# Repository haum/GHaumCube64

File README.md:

# GHaumCube64

Le GHaumCube64 est un jeu lumineux tridimentionnel sous forme de cube suspendu dans les airs.

État du projet : En cours

## Description générale

À l'heure actuelle, le projet est définit comme étant un cube de 64 (4×4×4) tåls (nom inventé pour désigner les éléments lumineux, munis chacun de trois leds multicolores adressables), orienté sur sa pointe et suspendu ; il y a aussi une manette de jeu à lui adjoindre. L'objectif est d'y programmer des jeux tels que morpion/snake/tron en 3D.

## Organisation des fichiers

```
<repo>
├── code
│   ├── cube <= Code du cube
│   └── remote <= Code de la télécommande/manette de jeu
│   └── Tal_test <= Code de test des LEDs
└── structure
    ├── placement
    │   ├── cube.blend <= disposition des tåls dans l'espace
    │   └── placement.scad <= disposition des tåls dans l'espace, d'un point de vue fabrication
    └── tal
        ├── tal.blend <= Modèle d'un tål complet
        ├── tal_bottom.stl.xz <= Export STL (compressé) de la partie basse
        ├── tal_top.stl.xz <= Export STL (compressé) de la partie haute
        └── Ball
            ├── support_led_Tal.FCStd <= Support LEDs FreeCAD file
            └── support_led_Tal.stl <= Export STL du support de LEDs
```

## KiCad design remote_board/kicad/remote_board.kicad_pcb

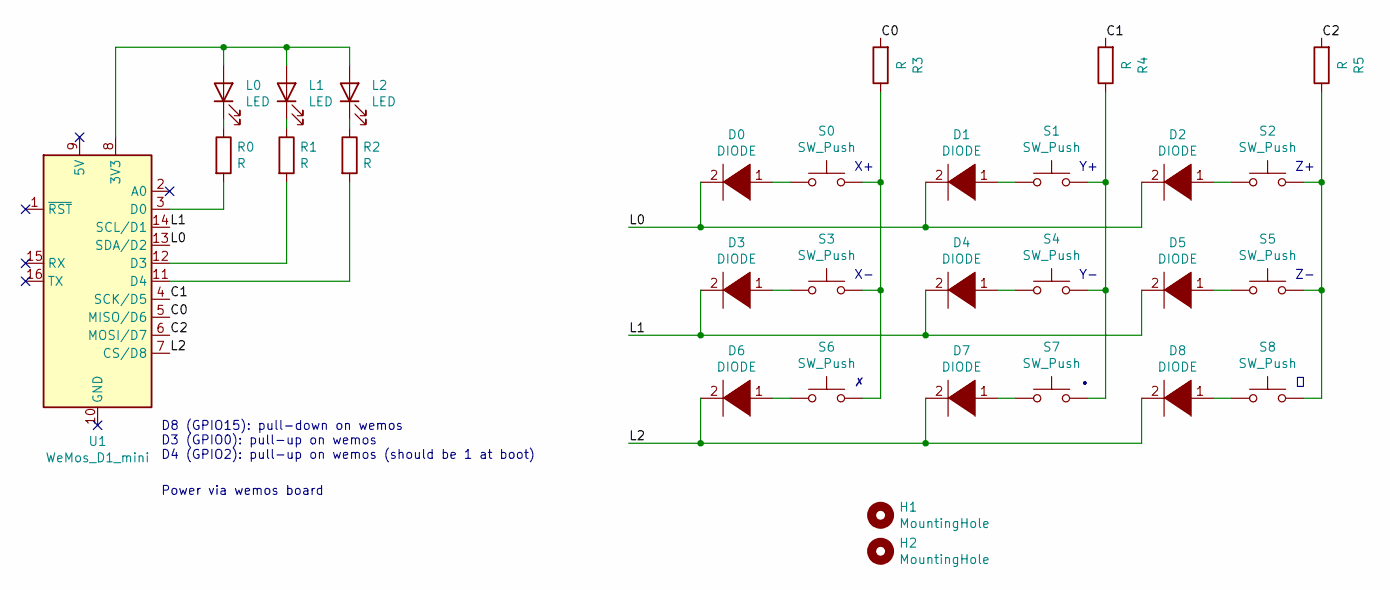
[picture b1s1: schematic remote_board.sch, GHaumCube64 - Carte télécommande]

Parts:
D0, D1, D2, D3, D4, D5, D6, D7, D8: DIODE; D_DO-35_SOD27_P10.16mm_Horizontal
H1, H2: MountingHole; MountingHole_5.3mm_M5
L0, L1, L2: LED; LED_D3.0mm
R0, R1, R2, R3, R4, R5: R; R_Axial_DIN0207_L6.3mm_D2.5mm_P15.24mm_Horizontal
S0, S1, S2, S3, S4, S5, S6, S7, S8: SW_Push; SW_PUSH_5mm_2pins
U1: WeMos_D1_mini; WEMOS_D1_mini_light

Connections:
/C0: R3.2, U1.5 (MISO/D6)
/C1: R4.2, U1.4 (SCK/D5)
/C2: R5.2, U1.6 (MOSI/D7)
/L0: D0.2 (A), D1.2 (A), D2.2 (A), U1.13 (SDA/D2)
/L1: D3.2 (A), D4.2 (A), D5.2 (A), U1.14 (SCL/D1)
/L2: D6.2 (A), D7.2 (A), D8.2 (A), U1.7 (CS/D8)
unnamed: D0.1 (K), S0.1
unnamed: D1.1 (K), S1.1
unnamed: D2.1 (K), S2.1
unnamed: D3.1 (K), S3.1
unnamed: D4.1 (K), S4.1
unnamed: D5.1 (K), S5.1
unnamed: D6.1 (K), S6.1
unnamed: D7.1 (K), S7.1
unnamed: D8.1 (K), S8.1
unnamed: L0.1 (K), R0.1
unnamed: L0.2 (A), L1.2 (A), L2.2 (A), U1.8 (3V3)
unnamed: L1.1 (K), R1.1
unnamed: L2.1 (K), R2.1
unnamed: R0.2, U1.3 (D0)
unnamed: R1.2, U1.12 (D3)
unnamed: R2.2, U1.11 (D4)
unnamed: R3.1, S0.2, S3.2, S6.2
unnamed: R4.1, S1.2, S4.2, S7.2
unnamed: R5.1, S2.2, S5.2, S8.2

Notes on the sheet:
D8 (GPIO15): pull-down on wemos D3 (GPIO0): pull-up on wemos D4 (GPIO2): pull-up on wemos (should be 1 at boot)
Power via wemos board

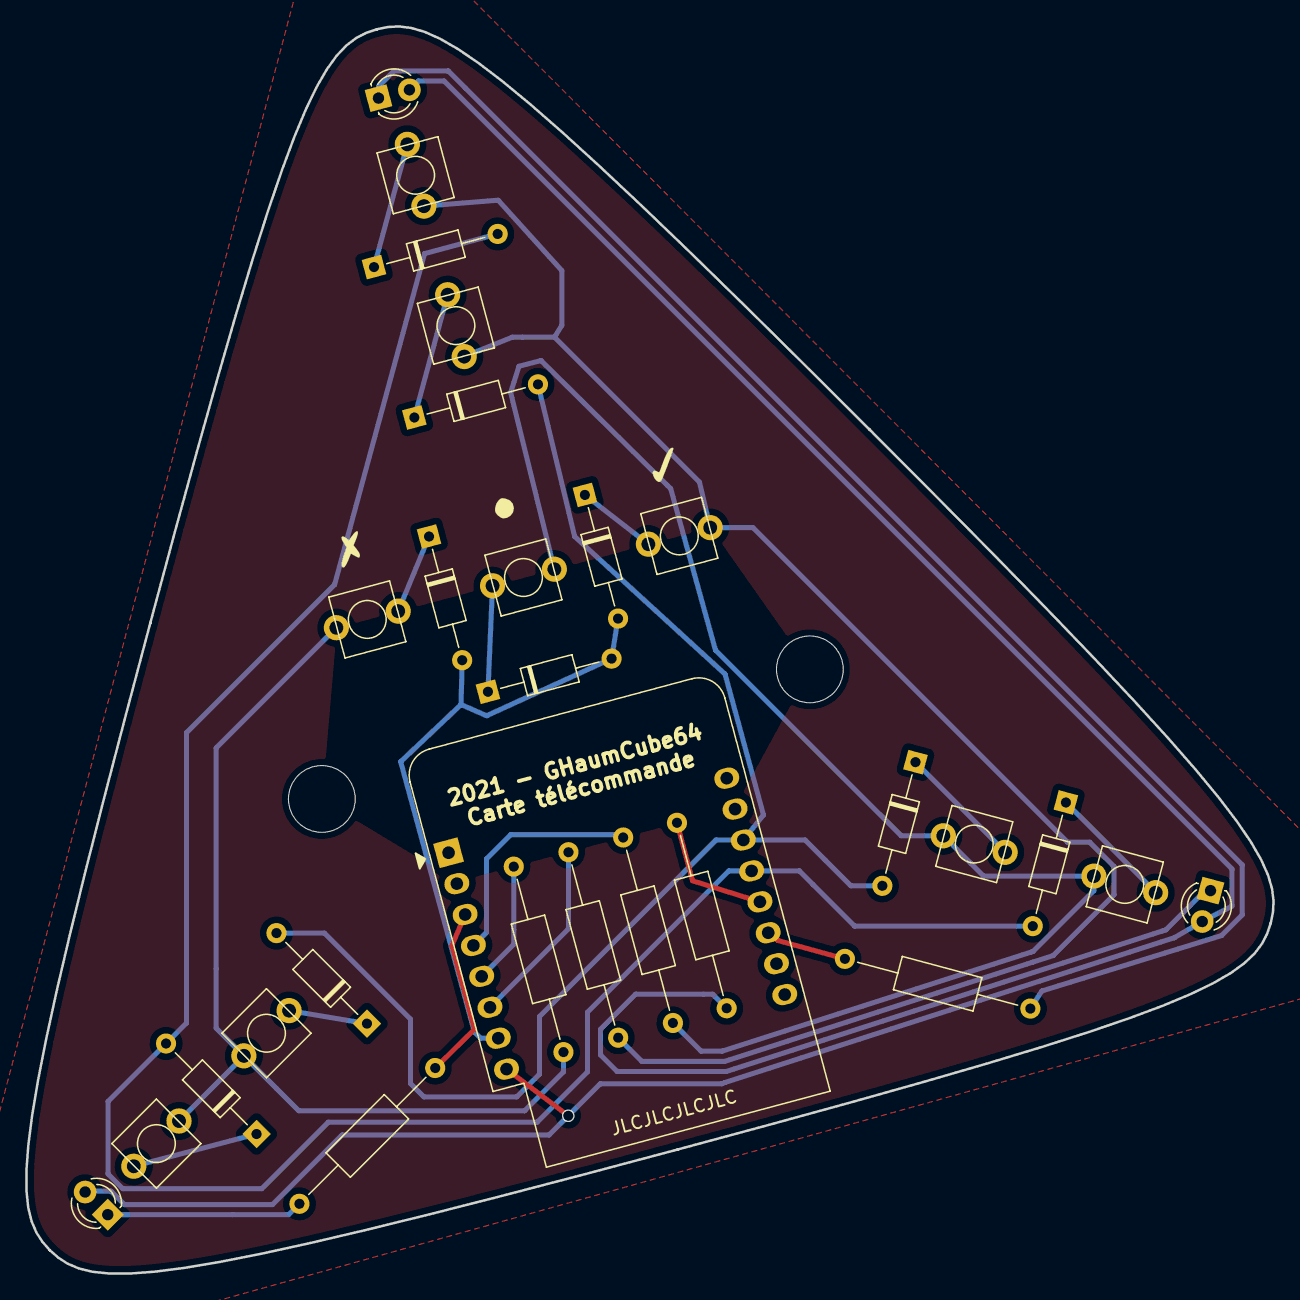
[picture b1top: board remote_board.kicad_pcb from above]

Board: 2 copper layers, 99.0 x 99.0 mm, 30 parts (0 on the bottom side), 25 nets.

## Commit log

2020-06-11 Add blender model of tål
2020-06-11 Add STL exports of tål
2020-06-11 Add visual expected 3D placement of the tåls in blender format
2020-06-11 Add structure placeholders for the code
2020-06-11 Add general README
2021-02-09 Update the model of tål for better printing
2021-09-09 add LEDs support for Tal flower remplacement
2021-09-09 simple code for testing LEDs
2021-09-09 Add scad to check dimentions
2021-09-10 Add remote kicad project
2021-09-10 Change structure to real dimention in scad file Add fabrication doc
2021-09-11 add gitignore file update fab doc
2021-09-12 Update remote kicad schematic
    Fixes from prototype:
    - invert C1 & L2 (D8 always measures LOW level)
    - invert leds on D3/D4 (for the builtin led to be on Z)
2021-09-12 Change button footprint in remote board
2021-09-12 Change component placement in remote board
2021-09-12 Change meaning of left/right buttons in remote board
2021-09-12 Add sketch to test hardware of the remote board
2021-09-12 Add schematic of remote board as PDF
2021-09-12 Export gerbers for the remote board
2021-09-13 change in PCB design for fab needs
2021-09-17 More fab docs
2021-09-20 Add Tals place in model Updated docs for Fab
2021-09-20 idea for a 3dprinted piece for assembling parts
2021-10-11 Provide a base for a python controller
2021-10-12 Display led after fill() function
2021-10-13 Add a source name to the E1.31
2021-10-13 Typo in class controler description
2021-10-13 ajust gitignore
2021-10-13 more construction doc
2021-10-13 new branch / more generic controller [WIP]
2021-10-13 small name correction
2021-10-19 Update placement spec to match real prototype errors
2021-10-26 new dimention for connecteur_branches
2021-10-26 New controller code
2021-10-28 Update controller to correctly address taler
2021-10-29 support for ESP based control board
2021-10-29 adjustment in connecteur_branches part
2021-10-29 Stop all Tal at and of chaser function
2021-10-29 Stop all Tal at end of chaser function
2021-10-29 typo !
2021-10-30 inprouve stop function
2021-11-09 Add a base code for the remote used in the 24hc21 challenge
2021-11-09 maquette d'absraction pour la possition des leds
2021-11-09 Add TCP stream to get buttons and control leds for the 24hc21 challenge
2021-11-10 More variables set in TalController: First universe & Source name
2021-11-11 Remove obsolete Led_test test
2021-11-11 Change test animation
2021-11-16 Add simple spy screen for 24HC21 challenge
2021-11-16 Rename Tal_test folder to pc_controller_example
2021-11-16 Add an explicit source name to pc_controller_example
2021-11-16 Add reset example in pc_controller_example
2021-11-16 Make screen_spy react to USR1 signal with statistics print
2021-11-17 control sending thread before closing software
2021-11-18 Avoid println in 24hc21_challenge, because it sends two packets
2022-02-25 Document de présentation du GHAUMCube64
2022-06-29 Add graphical part of simulator
2022-06-29 Add sacn reception in simulator
2022-08-26 Add cut drawing for protective back of the remote board
2022-09-07 raccord de contruction pour une structure pliable
2022-09-07 suite raccord
2022-09-13 stl du raccord
2022-09-27 support charniere
2025-06-25 Add animation_by_sacn inspired by tictacthaum animations
2025-07-07 qlc+ files fixture definition for animation_by_sacn first show file
2025-07-24 Add __pycache__ in gitignore
2025-07-24 Migrate simulator to pyglet 2.1
2025-07-24 Add effect 21 blink in animation_by_sacn
2025-07-24 Add fading parameter to sacn message in animation_by_sacn
2025-07-24 Add fading color animations in animation_by_sacn
2025-07-29 new function for fixture
2025-07-29 use of fading in spectro_cube
2025-07-31 add new effect in fixture definition
2025-07-31 new spectral animator for color 1 in virtual console
